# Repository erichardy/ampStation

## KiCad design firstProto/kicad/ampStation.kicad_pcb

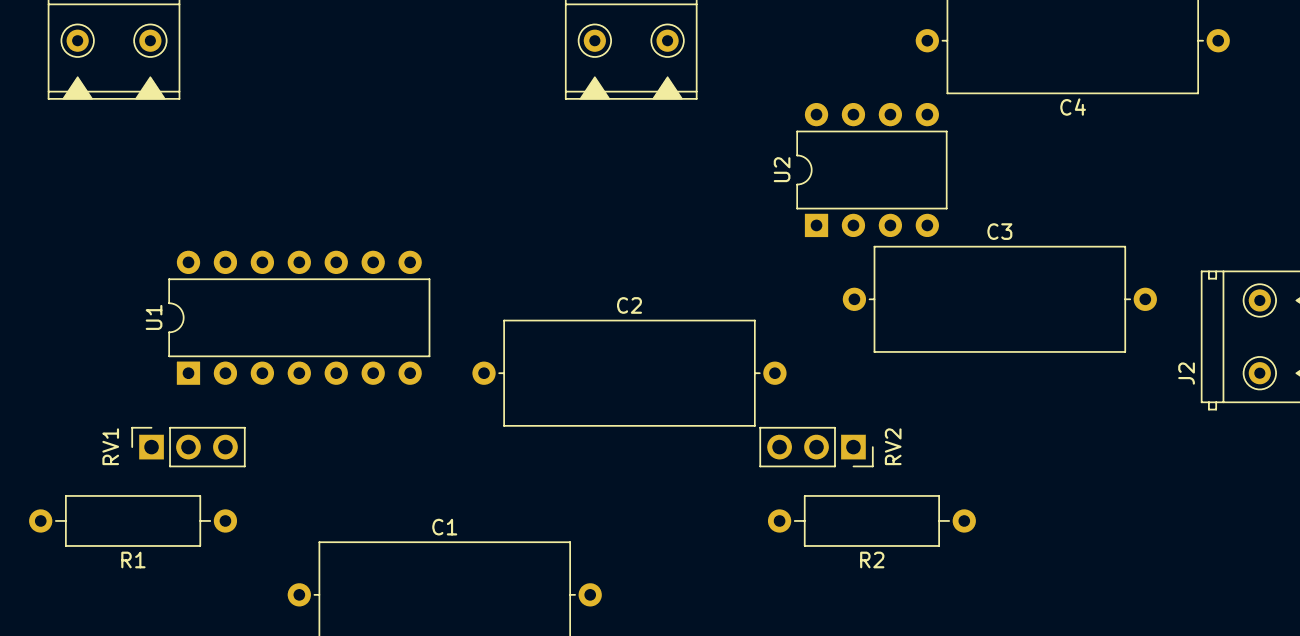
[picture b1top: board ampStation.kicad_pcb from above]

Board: 2 copper layers, 13 parts (0 on the bottom side), 9 nets.

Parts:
C1, C2, C3, C4: 10u; C_Axial_L17.0mm_D7.0mm_P20.00mm_Horizontal
J1: Entrée Signal; Bornier_2pts_L10mm_W9mm_P5mm
J2: Sortie uControl; Bornier_2pts_L10mm_W9mm_P5mm
J3: Alim5V; Bornier_2pts_L10mm_W9mm_P5mm
R1: 1k; R_Axial_DIN0309_L9.0mm_D3.2mm_P12.70mm_Horizontal
R2: 10k; R_Axial_DIN0309_L9.0mm_D3.2mm_P12.70mm_Horizontal
RV1: 10k; PinSocket_1x03_P2.54mm_Vertical
RV2: 100k; PinSocket_1x03_P2.54mm_Vertical
U1: TL074; DIP-14_W7.62mm
U2: MAX1044; DIP-8_W7.62mm

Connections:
GND: C1.2, C4.1, J1.2, J2.2, J3.2, RV2.1, RV2.2, U1.3, U2.3
unnamed: C1.1, C2.1, RV1.1, RV1.2, U1.1
unnamed: C2.2, J2.1, R2.2, RV2.3
unnamed: C3.1, U2.2
unnamed: C3.2, U2.4
unnamed: C4.2, U1.11, U2.5
unnamed: J1.1, R1.2
unnamed: R1.1, RV1.3, U1.2
VCC: J3.1, R2.1, U1.4, U2.8

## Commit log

2021-03-25 add firstProto kicad files
2021-03-25 kicad
2021-03-25 kicad suite
2021-03-26 kikad
2021-03-27 misc
2021-03-29 f proto2
2021-03-31 first code
2021-04-20 computations
2021-04-26 avec OLED
